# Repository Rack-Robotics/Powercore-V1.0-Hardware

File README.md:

# Rack Robotics Powercore EDM Power Supply Unit Hardware

This repository contains the hardware and electronics CAD for Rack Robotics's Powercore, an affordable, hackable transistor EDM power supply unit. It is released under the [Creative Commons CC BY-NC 4.0 license.](https://creativecommons.org/licenses/by-nc/4.0/legalcode)

## Overview

The Rack Robotics's Powercore V1 is a transistor-capacitor hybrid EDM power supply unit. The Powercore creates, maintains, and monitors electrical sparks in an EDM machine. It is designed to be affordable and hackable.

[Morlock's YouTube Video](https://www.youtube.com/watch?v=5CeCxkFVCdM)

[Original Kickstarter](https://www.kickstarter.com/projects/rackrobotics/powercore-cut-through-solid-metal-with-edm)

This repository contains KiCAD projects for EDM Motherboard [23.04.20] and EDM PCB Resistor [23.05.03]. As well as STEP and Fusion 360 archive files of the physical power supply. STLs and other files for 3D printer are on the [Rack Robotics printables](https://www.printables.com/@RackRoboticsO_631255/models).

## Installation

Clone the repository using the following command:

git clone https://github.com/rack-robotics/powercore-v1-hardware.git

## Contributing
We welcome contributions to this project. If you've found a bug or have a feature request, please open an issue. If you would like to improve the firmware, please fork the repository and create a pull request.

## License
This software is released by Rack Robotics, Inc. under the Creative Commons CC BY-NC 4.0 license.

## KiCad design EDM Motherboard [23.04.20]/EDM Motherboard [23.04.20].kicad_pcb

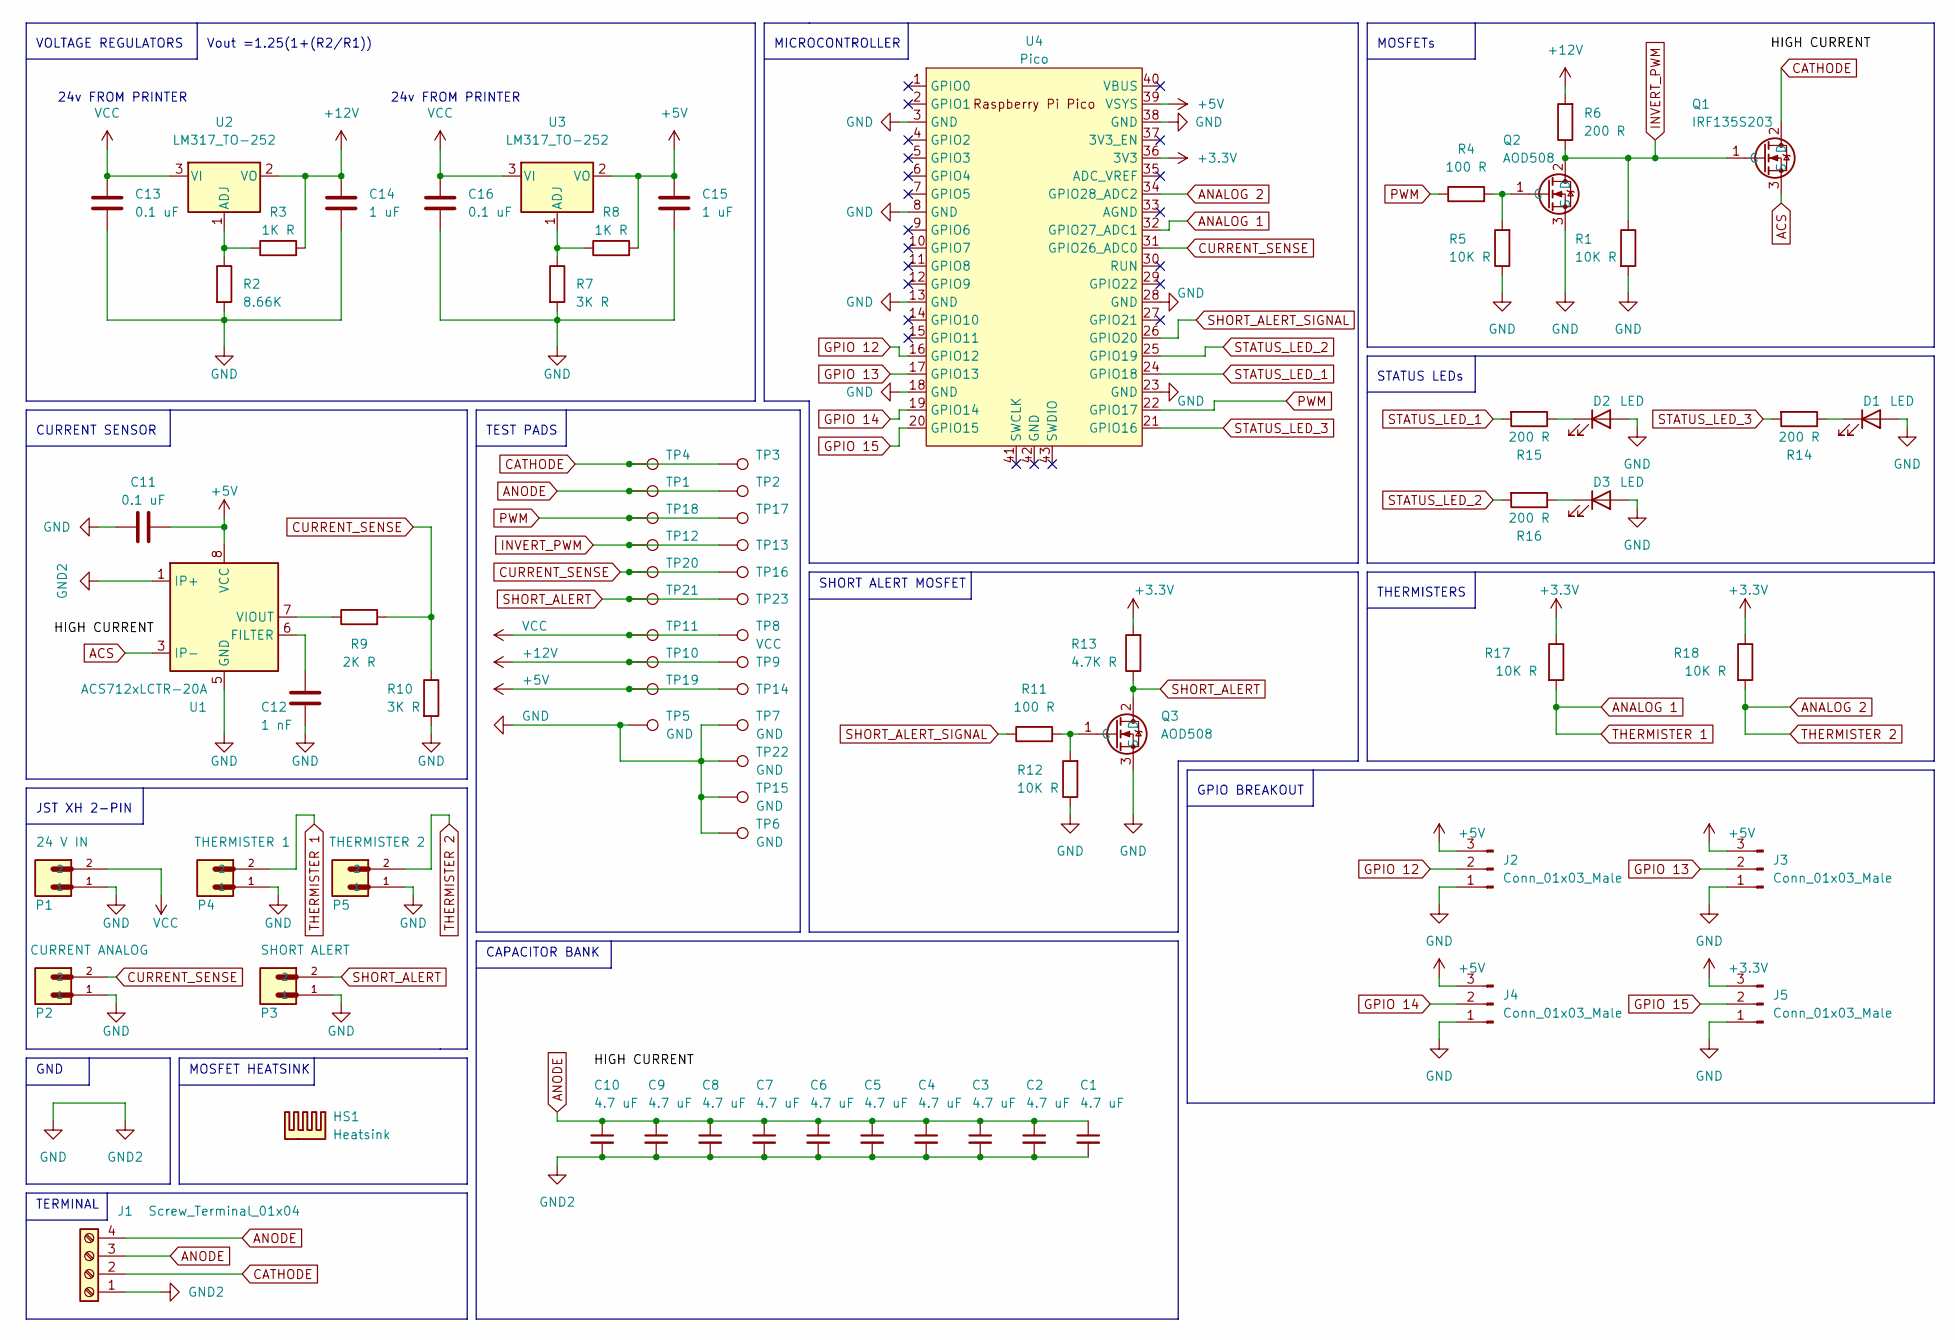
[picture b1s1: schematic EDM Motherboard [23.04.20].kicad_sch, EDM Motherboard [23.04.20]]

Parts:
C1, C2, C3, C4, C5, C6, C7, C8, C9, C10: 4.7 uF; C_1206_3216Metric; MFR Part# GRM31CC72A475KE11K; LCSC Part # C237304
C11, C13, C16: 0.1 uF; C_0805_2012Metric; LCSC Part # C28233
C12: 1 nF; C_0805_2012Metric; LCSC Part # C46653
C14, C15: 1 uF; C_0805_2012Metric; LCSC Part # C28323
D1, D2, D3: LED; LED_0603_1608Metric; LCSC Part # C2290
HS1: Heatsink; Heatsink_AAVID_573300D00010G_TO-263; DigiKey # 497-1574-1-ND
J1: Screw_Terminal_01x04; CUI_TB002-500-04BE; DigiKey # 102-6147-ND
J2, J3, J4, J5: Conn_01x03_Male; PinHeader_1x03_P2.54mm_Vertical; LCSC Part # C2937625
P1: 24 V IN; JST_S2B-XH-A(LF)(SN); LCSC Part # C157931
P2: CURRENT ANALOG; JST_S2B-XH-A(LF)(SN); LCSC Part # C157931
P3: SHORT ALERT; JST_S2B-XH-A(LF)(SN); LCSC Part # C157931
P4: THERMISTER 1; B2B-XH-A(LF)(SN); LCSC Part # C158012
P5: THERMISTER 2; B2B-XH-A(LF)(SN); LCSC Part # C158012
Q1: IRF135S203; TO-263-2; DigiKey # IRF135S203CT-ND
Q2, Q3: AOD508; TO-252-2; DigiKey # 785-1355-1-ND
R1, R5, R12, R17, R18: 10K R; R_1206_3216Metric; LCSC Part # C17902
R2: 8.66K; R_1206_3216Metric; LCSC Part # C245607
R3, R8: 1K R; R_1206_3216Metric; LCSC Part # C4410
R4, R11: 100 R; R_1206_3216Metric; LCSC Part # C17901
R6: 200 R; R_1206_3216Metric; DigiKey # 311-1.00KFRCT-ND
R7, R10: 3K R; R_1206_3216Metric; LCSC Part # C132648
R9: 2K R; R_1206_3216Metric; LCSC Part # C133543
R13: 4.7K R; R_1206_3216Metric; LCSC Part # C137262
R14, R15, R16: 200 R; R_1206_3216Metric; LCSC Part # C114939
TP1, TP2, TP3, TP4: CATHODE; TestPoint_Pad_1.5x1.5mm
TP5, TP6, TP7, TP15, TP22: GND; TestPoint_Pad_1.5x1.5mm
TP8, TP11: VCC; TestPoint_Pad_1.5x1.5mm
TP9, TP10: +12v; TestPoint_Pad_1.5x1.5mm
TP12, TP13: INVRT_PWM; TestPoint_Pad_1.5x1.5mm
TP14, TP19: +5V; TestPoint_Pad_1.5x1.5mm
TP16, TP20: CURRENT ANALOG; TestPoint_Pad_1.5x1.5mm
TP17, TP18: PWM; TestPoint_Pad_1.5x1.5mm
TP21, TP23: SHORT ALERT; TestPoint_Pad_1.5x1.5mm
U1: ACS712xLCTR-20A; SOIC-8_3.9x4.9mm_P1.27mm; LCSC Part # C10681
U2, U3: LM317_TO-252; TO-252-2; LCSC Part # C75510
U4: Pico; RPi_Pico_SMD_TH; DigiKey # 2648-SC0915CT-ND

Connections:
+3.3V: J5.3, R13.2, R17.1, R18.1, U4.36 (3V3)
+5V: C11.1, C15.1, J2.3, J3.3, J4.3, R8.2, TP14.1, TP19.1, U1.8 (VCC), U3.2 (VO), U4.39 (VSYS)
+12V: C14.1, R3.2, R6.2, TP9.1, TP10.1, U2.2 (VO)
ACS: Q1.3 (S), U1.3 (IP-), U1.4 (IP-)
ANALOG 1: P4.2, R17.2, U4.32 (GPIO27_ADC1)
ANALOG 2: P5.2, R18.2, U4.34 (GPIO28_ADC2)
ANODE: C1.1, C2.1, C3.1, C4.1, C5.1, C6.1, C7.1, C8.1, C9.1, C10.1, J1.3, J1.4, TP1.1, TP2.1
CATHODE: J1.2, Q1.2 (D), TP3.1, TP4.1
CURRENT_SENSE: P2.2, R9.2, R10.1, TP16.1, TP20.1, U4.31 (GPIO26_ADC0)
GND: C1.2, C2.2, C3.2, C4.2, C5.2, C6.2, C7.2, C8.2, C9.2, C10.2, C11.2, C12.1, C13.2, C14.2, C15.2, C16.2, D1.2 (A), D2.2 (A), D3.2 (A), J1.1, J2.1, J3.1, J4.1, J5.1, P1.1, P2.1, P3.1, P4.1, P5.1, Q2.3 (S), Q3.3 (S), R1.2, R2.2, R5.1, R7.2, R10.2, R12.1, TP5.1, TP6.1, TP7.1, TP15.1, TP22.1, U1.1 (IP+), U1.2 (IP+), U1.5 (GND), U4.3 (GND), U4.8 (GND), U4.13 (GND), U4.18 (GND), U4.23 (GND), U4.28 (GND), U4.38 (GND)
GPIO 12: J2.2, U4.16 (GPIO12)
GPIO 13: J3.2, U4.17 (GPIO13)
GPIO 14: J4.2, U4.19 (GPIO14)
GPIO 15: J5.2, U4.20 (GPIO15)
INVERT_PWM: Q1.1 (G), Q2.2 (D), R1.1, R6.1, TP12.1, TP13.1
unnamed: C12.2, U1.6 (FILTER)
unnamed: D2.1 (K), R15.1
unnamed: D1.1 (K), R14.1
unnamed: D3.1 (K), R16.1
unnamed: Q2.1 (G), R4.2, R5.2
unnamed: Q3.1 (G), R11.2, R12.2
unnamed: R2.1, R3.1, U2.1 (ADJ)
unnamed: R7.1, R8.1, U3.1 (ADJ)
unnamed: R9.1, U1.7 (VIOUT)
PWM: R4.1, TP17.1, TP18.1, U4.22 (GPIO17)
SHORT_ALERT: P3.2, Q3.2 (D), R13.1, TP21.1, TP23.1
SHORT_ALERT_SIGNAL: R11.1, U4.26 (GPIO20)
STATUS_LED_1: R15.2, U4.24 (GPIO18)
STATUS_LED_2: R16.2, U4.25 (GPIO19)
STATUS_LED_3: R14.2, U4.21 (GPIO16)
VCC: C13.1, C16.1, P1.2, TP8.1, TP11.1, U2.3 (VI), U3.3 (VI)

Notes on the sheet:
TEST PADS
MICROCONTROLLER
JST XH 2-PIN
THERMISTERS
CAPACITOR BANK
TERMINAL
24v FROM PRINTER
SHORT ALERT MOSFET
GPIO BREAKOUT
Vout =1.25(1+(R2/R1))
MOSFET HEATSINK
STATUS LEDs
GND
VOLTAGE REGULATORS
CURRENT SENSOR
MOSFETs

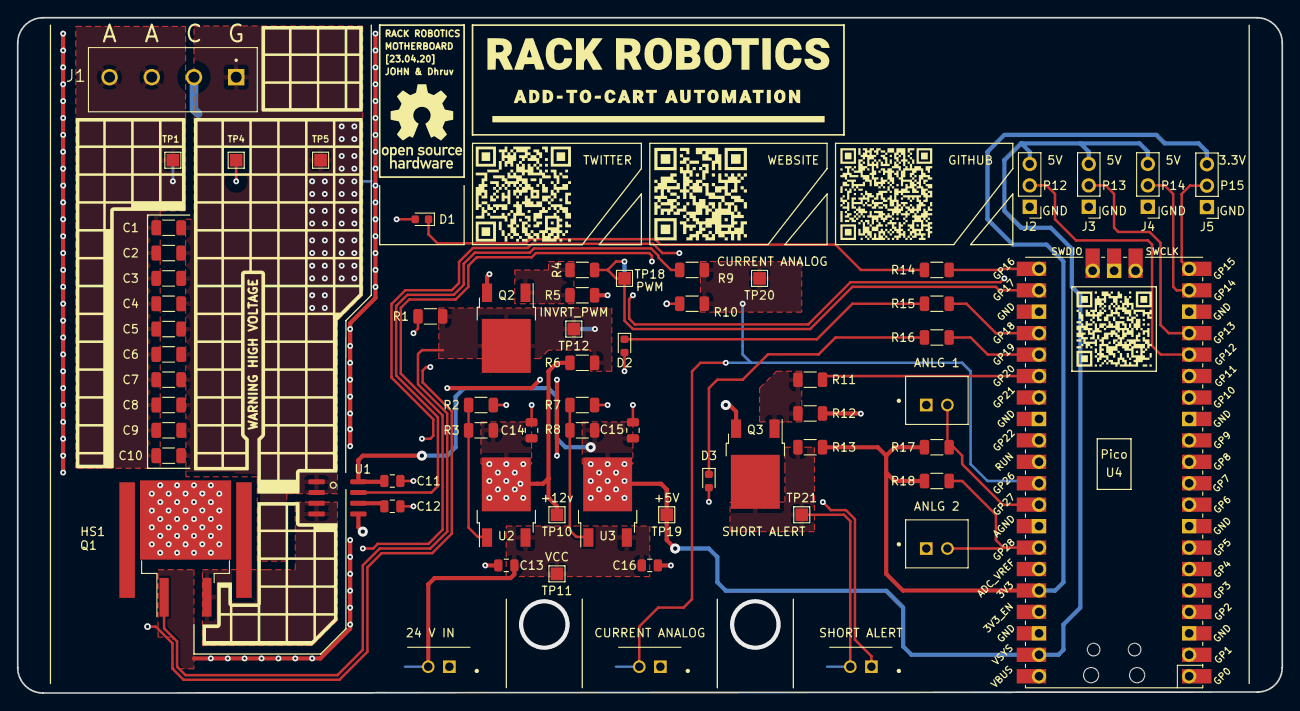
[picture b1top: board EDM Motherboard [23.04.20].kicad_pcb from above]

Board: 2 copper layers, 149.8 x 80.0 mm, 78 parts (0 on the bottom side), 31 nets.

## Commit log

2023-08-01 Added photos of boards and schematics
2023-12-29 Added HTML BoM
